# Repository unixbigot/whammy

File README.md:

# Whammy - A bluetooth expression pedal using tilt angle to trigger effects

The Whammy system consists of two pieces of hardware, both of which
are compiled from this repository.    Much of the source code is
common.

The software runs atop the Zephyr real time operating system, and
makes use of an application module for Zephyr named 'ztacx' (also
written by the author of whammy).

The hardware components are

## Whammy Puck

A bluetooth Low-Energy (BLE aka Bluetooth 4, which is a totally
different protocol than older versions of bluetooth) 
peripheral that contains an accelerometer and magnetometer.

In BLE you can think of "peripheral" as meaning "server".
It exposes all the sensors as "characteristics", characteristics being
in essence "pages" that the server can serve.

The puck is battery powered, and attaches to your instrument via a
suction cup.   The battery should last many days (but should be
disconnected when not in use).

Bluetooth characteristics are identified by UUIDs, which can be 
from a standard service profile, or vendor specific.

For ease of use we use the standard "Generic Level" characteristic ID 
to serve the "wham factor".   Many other sensors and details are also
presented.   You can test the puck using the 'nrfConnect' app on android or iphone to
scan for the device and browse these characteristics.  (Note the device will not be
accessible from your phone if something else is already connected to
it, like the receiver).

The puck has an LED.   1 second blink rate means "waiting for
connection", 5 second blink rate means "somebody is connected".

The puck is configured to expose the "X-Axis Acceleration" in
cm/sec/sec as the "generic level".  For tilt this would range from
-980 (normal acceleration due to gravity), through zero (the device is
perfectly flat therefore there is no acceleration in the X-direction),
to 980 (1G or 9.8m/s/s, x-axis aligned straight down).   Under conditions of shock or
shaking acceleration could be much higher (the device is configured
for a max of 2G).

## Whammy Receiver

The receiver has a colour (RGB) LED and a digital-to-analog converter (DAC), built
into the back of a Tip-Ring-Sleeve phono plug.   Sleeve is ground, Tip
is 5-12 volts input, and Ring is analog out (0-to-3.3 volts).

The receiver is intended to plug into the "expression pedal" jack of
any audo effect box.

The receiver acts as a "bluetooth central" device (bluetooth-speak for
client).   The receiver scans for a peripheral named "whammy puck"
(LED will be orange).   When it connects (LED goes green) it looks for
the "Generic Level" characteristic, and monitors its value.   Whenever
the value changes the receiver blinks the LED blue and updates the
DAC.

The receiver converts the "generic level" range of [-980, 980] to the
DAC's parameter range [0,4095].  The DAC expresses its parameter as a
voltage, from [0, 3.3v].

It is intended that your effect be configured to treat this analog
voltage as an input to its effect processing.

A test fixture is supplied which uses a USB cable to supply 5 volts to
the receiver, and displays the output voltage on a voltmeter.

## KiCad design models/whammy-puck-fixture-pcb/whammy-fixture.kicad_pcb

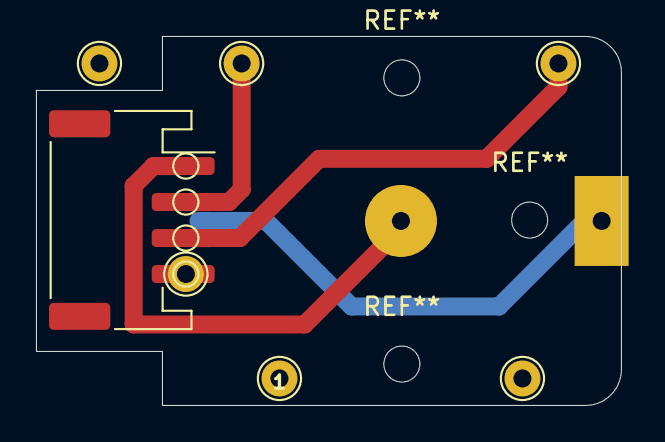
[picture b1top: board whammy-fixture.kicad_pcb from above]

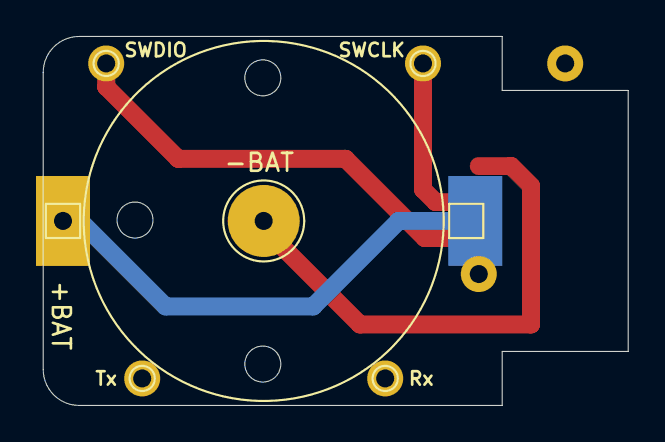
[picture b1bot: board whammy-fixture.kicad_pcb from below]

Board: 2 copper layers, 32.5 x 20.5 mm, 11 parts (7 on the bottom side), 4 nets.

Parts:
J2, J3: +BAT; TestPoint_Pad_1.5x1.5mm
J4: -BAT; TestPoint_Pad_D4.0mm
TP1: GND; TestPoint_Pad_D1.0mm
TP2: VDD; TestPoint_Pad_D1.0mm
TP3, TP10: SWDIO; TestPoint_Pad_D1.0mm
TP4: SWDCLK; TestPoint_Pad_D1.0mm
TP11: SWCLK; TestPoint_Pad_D1.0mm
TP12: Tx; TestPoint_Pad_D1.0mm
TP13: Rx; TestPoint_Pad_D1.0mm

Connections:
+BATT: J2.1, J3.1, TP2.1
-BATT: J4.1, TP1.1
/SWCLK: TP4.1, TP11.1
/SWDIO: TP3.1, TP10.1

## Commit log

2024-10-13 Sender and receiver for the 'whammy' wireless instrumental expression pedal
2024-10-13 Whitepsace, plus plumb expression_level variable through to DAC if enabled
2024-10-16 Add readme, commit final code updates
